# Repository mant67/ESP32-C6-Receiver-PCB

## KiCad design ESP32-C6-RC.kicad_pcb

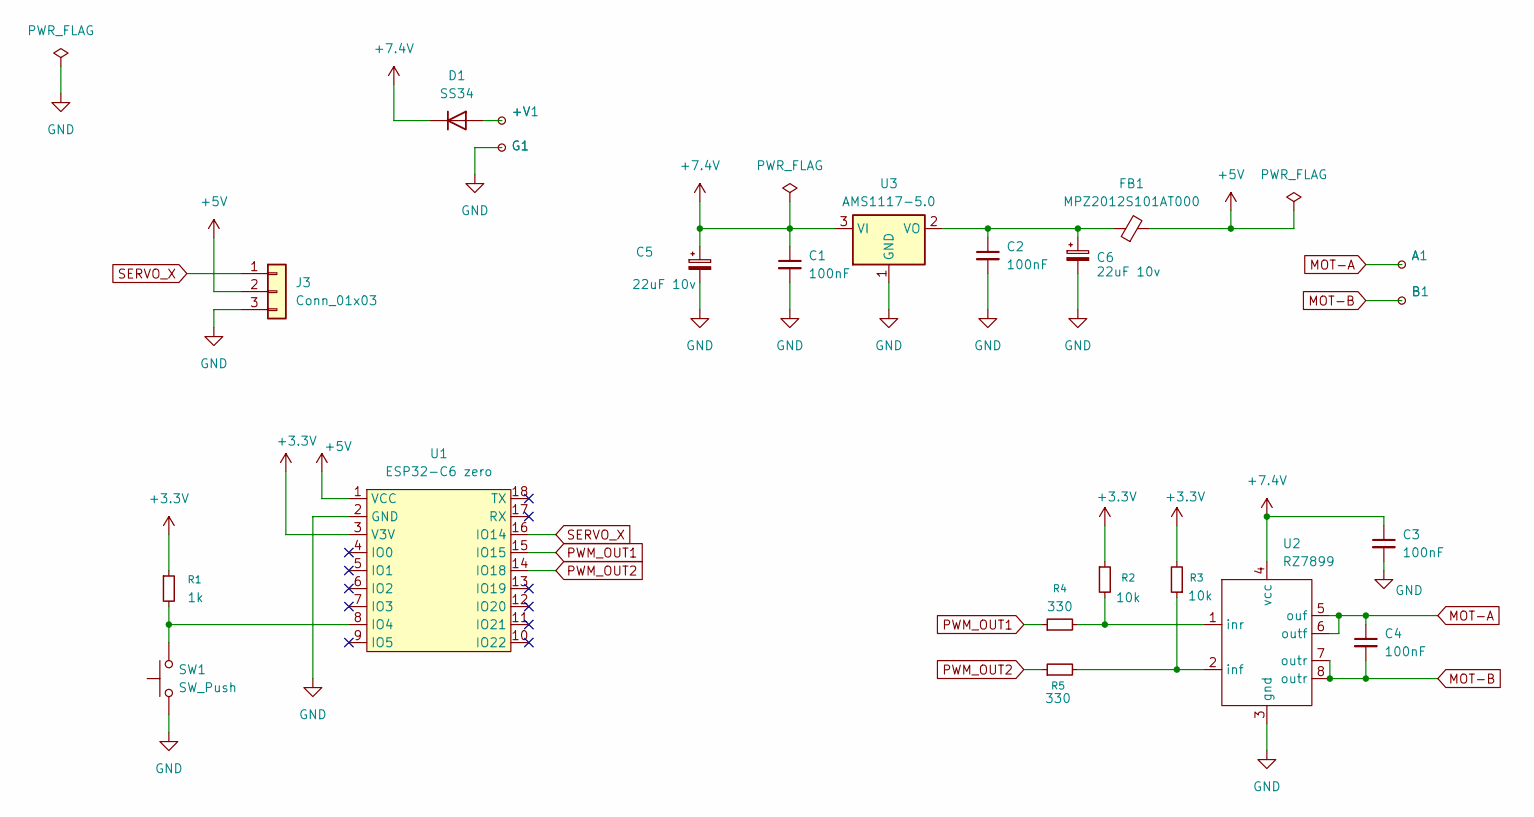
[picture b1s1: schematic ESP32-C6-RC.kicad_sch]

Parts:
+V1: +V; TestPoint_THTPad_D1.5mm_Drill0.7mm
A1: A; TestPoint_THTPad_D1.5mm_Drill0.7mm
B1: B; TestPoint_THTPad_D1.5mm_Drill0.7mm
C1, C2, C3, C4: 100nF; C_0805_2012Metric_Pad1.18x1.45mm_HandSolder
C5, C6: 22uF 10v; CP_EIA-3528-12_Kemet-T_HandSolder
D1: SS34; D_SMA
FB1: MPZ2012S101AT000; D_0805_2012Metric_Pad1.15x1.40mm_HandSolder
G1: G1; TestPoint_THTPad_D1.5mm_Drill0.7mm
J3: Conn_01x03; PinHeader_1x03_P2.54mm_Vertical
R1: 1k; R_0805_2012Metric_Pad1.20x1.40mm_HandSolder
R2, R3: 10k; R_0805_2012Metric_Pad1.20x1.40mm_HandSolder
R4, R5: 330; R_0805_2012Metric_Pad1.20x1.40mm_HandSolder
SW1: SW_Push; SW_SPST_B3S-1000
U1: ESP32-C6 zero; Waveshare-ESP32-C6-Zero
U2: RZ7899; SOP-8_3.76x4.96mm_P1.27mm
U3: AMS1117-5.0; SOT-89-3_Handsoldering

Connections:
+3.3V: R1.1, R2.1, R3.2, U1.3 (V3V)
+5V: FB1.2, J3.2, U1.1 (VCC)
+7.4V: C1.1, C3.1, C5.1, D1.1 (K), U2.4 (vcc), U3.3 (VI)
GND: C1.2, C2.2, C3.2, C5.2, C6.2, G1.1, J3.3, SW1.1, U1.2 (GND), U2.3 (gnd), U3.1 (GND)
MOT-A: A1.1, C4.1, U2.5 (ouf), U2.6 (outf)
MOT-B: B1.1, C4.2, U2.7 (outr), U2.8 (outr)
unnamed: +V1.1, D1.2 (A)
unnamed: R1.2, SW1.2, U1.8 (IO4)
unnamed: R3.1, R5.2, U2.2 (inf)
unnamed: R2.2, R4.2, U2.1 (inr)
unnamed: C2.1, C6.1, FB1.1, U3.2 (VO)
PWM_OUT1: R4.1, U1.15 (IO15)
PWM_OUT2: R5.1, U1.14 (IO18)
SERVO_X: J3.1, U1.16 (IO14)

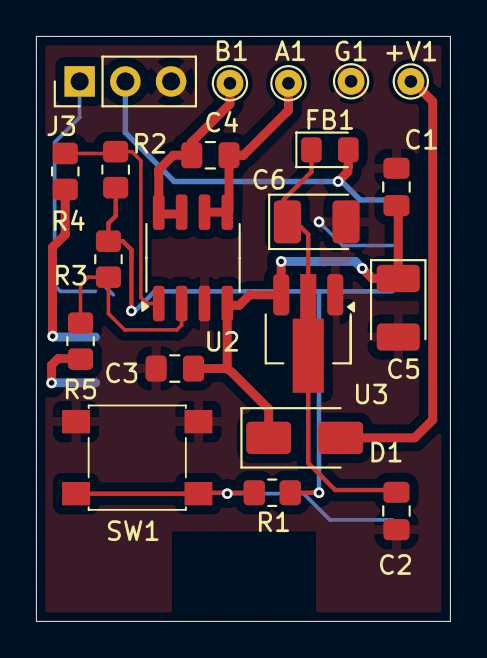
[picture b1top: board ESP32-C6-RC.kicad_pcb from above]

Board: 2 copper layers, 23.0 x 32.5 mm, 22 parts (1 on the bottom side), 14 nets.

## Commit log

2025-09-17 update schemtics and pcb
2025-09-18 fix pcb
